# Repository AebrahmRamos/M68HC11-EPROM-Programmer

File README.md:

# M68HC11-EPROM-Programmer

## Part 1: EPROM Reader

### Overview

This project implements an EPROM reader using the M68HC11 microcontroller and a 2764 EPROM chip. The system reads the first 25 bytes of data stored in the EPROM and transmits it to a host computer via serial communication for display in both hexadecimal and ASCII formats.

### Hardware Configuration

The hardware setup maps the M68HC11 ports to the 2764 EPROM pins as follows:

- **Port B (PB0-PB7)**: Connected to EPROM address inputs A0-A7
- **Port C (PC0-PC7)**: Connected to EPROM data outputs Q0-Q7
- **Port A (PA5, PA6)**: Control signals for Chip Enable (CE) and Output Enable (OE)
- **Upper Address Lines (A8-A12)**: Grounded to restrict addressable space to the first 256 bytes

The EPROM operates with a 5V supply and has an access time of 180-250ns depending on the speed grade.

### Software Implementation

The system consists of two main components:

#### Assembly Program (programmer.asm)

The M68HC11 assembly program performs the following steps:

1. **Initialization**: Sets up the stack pointer and forces the device into single-chip mode
2. **Port Configuration**: Configures Port C as input and sets control pins to inactive (HIGH)
3. **Serial Setup**: Initializes the SCI (Serial Communication Interface) to 9600 baud
4. **Startup Delay**: Implements a `LONG_DELAY` routine to allow the bootloader time to switch baud rates
5. **Read Loop**: Iterates 25 times to:
   - Assert the address on Port B
   - Activate control signals (pull CE and OE LOW)
   - Read the data byte from Port C
   - Send the byte to the PC via `SEND_SERIAL` subroutine
   - Deactivate control signals (pull CE and OE HIGH)

#### Python Bootloader (HC11_BL-ASCII.py)

The modified bootloader script:

- Loads the assembly program into the HC11's RAM via serial at 1200 baud
- Switches the serial port to 9600 baud after successful echo-back
- Calls `read_eprom_data()` to receive and display the 25 bytes
- Displays output in hexadecimal format (8 bytes per line)
- Displays output in ASCII format (replaces non-printable characters with ".")

### Key Challenge: Baud Rate Synchronization

During initial testing, a race condition occurred where the HC11 began transmitting data before the bootloader could switch from 1200 to 9600 baud. This resulted in corrupted or "ghost" byte values.

**Solution**: Implemented the `LONG_DELAY` subroutine after baud rate configuration to waste CPU cycles, giving the bootloader sufficient time to reinitialize the serial connection at 9600 baud before the read loop begins.

### Results

The system successfully:

- Reads the first 25 bytes from the 2764 EPROM
- Transmits data error-free via serial communication
- Displays data in both hexadecimal and ASCII formats
- Handles the 0xFF value gracefully by displaying it as "." in ASCII output (since ASCII is a 7-bit standard supporting only values 0-127)

### Materials

- 1x M68HC11 Interface Board
- 1x 2764 EPROM
- 1x Breadboard
- 2x Power Supplies
- 5x 10Kohm Resistors
- 1x Oscilloscope
- 1x VOM (Voltmeter/Ohmmeter)
- 1x Computer System

### Usage

1. Assemble the assembly code into an S19 file
2. Run the bootloader script: `python HC11_BL-ASCII.py -c /dev/ttyUSB0 -i programmer.s19`
3. Press RESET on the HC11 board when prompted
4. The program will load, switch baud rates, and display the EPROM data

### Recommendations for Future Work

While the current implementation successfully resolves the baud rate race condition, it uses a fixed delay that is not deterministic. A more robust approach would implement a software handshake using interrupts, similar to TCP's three-way handshake. This would ensure 100% data synchronization without relying on timing assumptions that may fail on slower systems or under heavy CPU load.

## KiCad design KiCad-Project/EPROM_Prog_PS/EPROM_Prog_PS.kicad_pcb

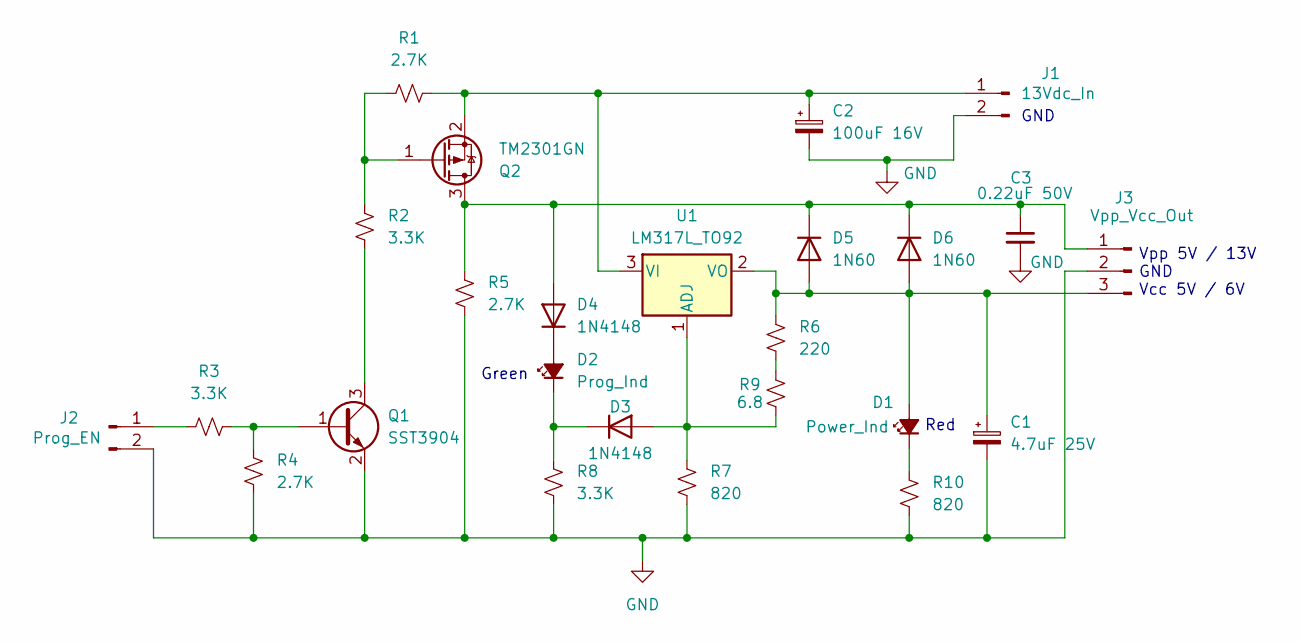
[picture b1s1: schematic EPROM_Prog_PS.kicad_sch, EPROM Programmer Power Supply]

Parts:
C1: 4.7uF 25V; CP_Radial_D5.0mm_P2.00mm
C2: 100uF 16V; CP_Radial_D6.3mm_P2.50mm
C3: 0.22uF 50V; C_Disc_D6.0mm_W4.4mm_P5.00mm
D1: Power_Ind; LED_D5.0mm
D2: Prog_Ind; LED_D5.0mm
D3, D4: 1N4148; D_DO-35_SOD27_P7.62mm_Horizontal
D5, D6: 1N60; D_DO-35_SOD27_P7.62mm_Horizontal
J1: 13Vdc_In; PinHeader_1x02_P2.54mm_Vertical
J2: Prog_EN; PinHeader_1x02_P2.54mm_Vertical
J3: Vpp_Vcc_Out; PinHeader_1x03_P2.54mm_Vertical
Q1: SST3904; SOT-23
Q2: TM2301GN; SOT-23
R1, R4, R5: 2.7K; R_Axial_DIN0207_L6.3mm_D2.5mm_P10.16mm_Horizontal
R2, R3, R8: 3.3K; R_Axial_DIN0207_L6.3mm_D2.5mm_P10.16mm_Horizontal
R6: 220; R_Axial_DIN0207_L6.3mm_D2.5mm_P10.16mm_Horizontal
R7, R10: 820; R_Axial_DIN0207_L6.3mm_D2.5mm_P10.16mm_Horizontal
R9: 6.8; R_Axial_DIN0207_L6.3mm_D2.5mm_P10.16mm_Horizontal
U1: LM317L_TO92; TO-92_Inline

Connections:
GND: C1.2, C2.2, C3.2, J1.2, J2.2, J3.2, Q1.2 (E), R4.2, R5.2, R7.2, R8.2, R10.2
unnamed: C1.1, D1.2 (A), D5.2 (A), D6.2 (A), J3.3, R6.1, U1.2 (VO)
unnamed: D1.1 (K), R10.1
unnamed: D2.2 (A), D4.1 (K)
unnamed: D2.1 (K), D3.1 (K), R8.1
unnamed: D3.2 (A), R7.1, R9.1, U1.1 (ADJ)
unnamed: C3.1, D4.2 (A), D5.1 (K), D6.1 (K), J3.1, Q2.3 (D), R5.1
unnamed: C2.1, J1.1, Q2.2 (S), R1.1, U1.3 (VI)
unnamed: J2.1, R3.1
unnamed: Q1.1 (B), R3.2, R4.1
unnamed: Q1.3 (C), R2.2
unnamed: Q2.1 (G), R1.2, R2.1
unnamed: R6.2, R9.2

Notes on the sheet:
Green
Vpp 5V / 13V GND Vcc 5V / 6V
GND
Red

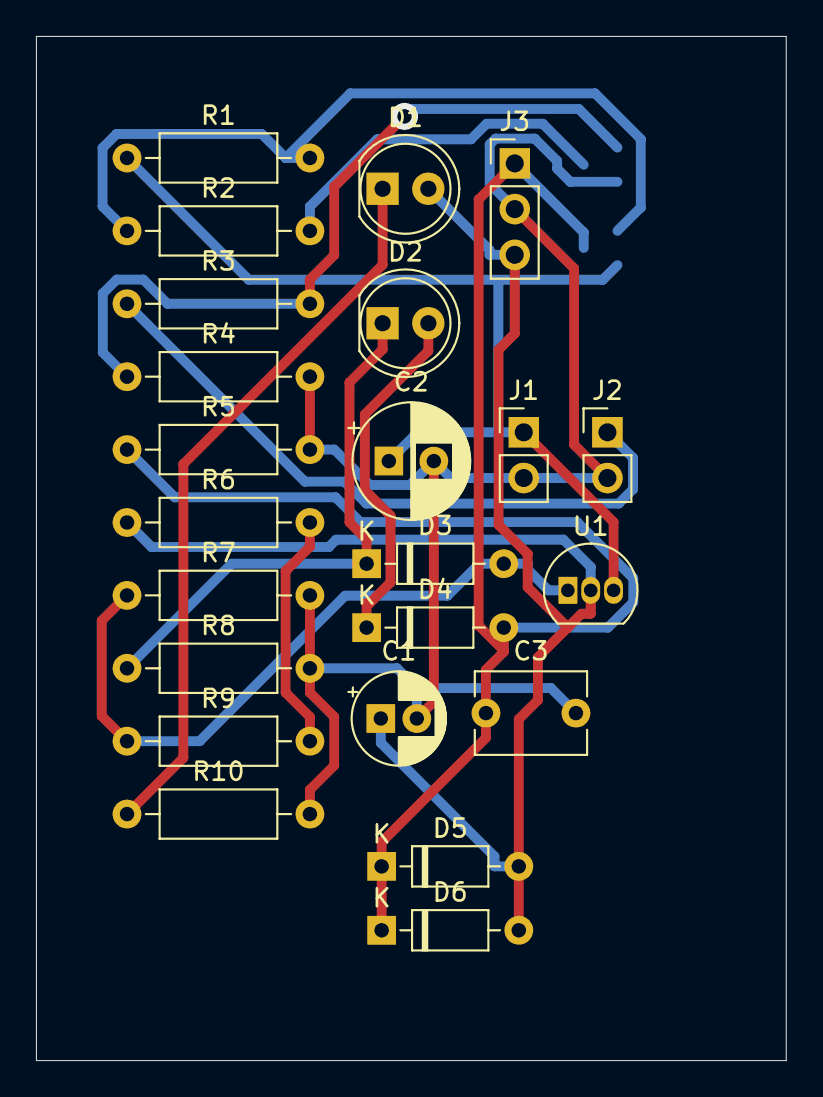
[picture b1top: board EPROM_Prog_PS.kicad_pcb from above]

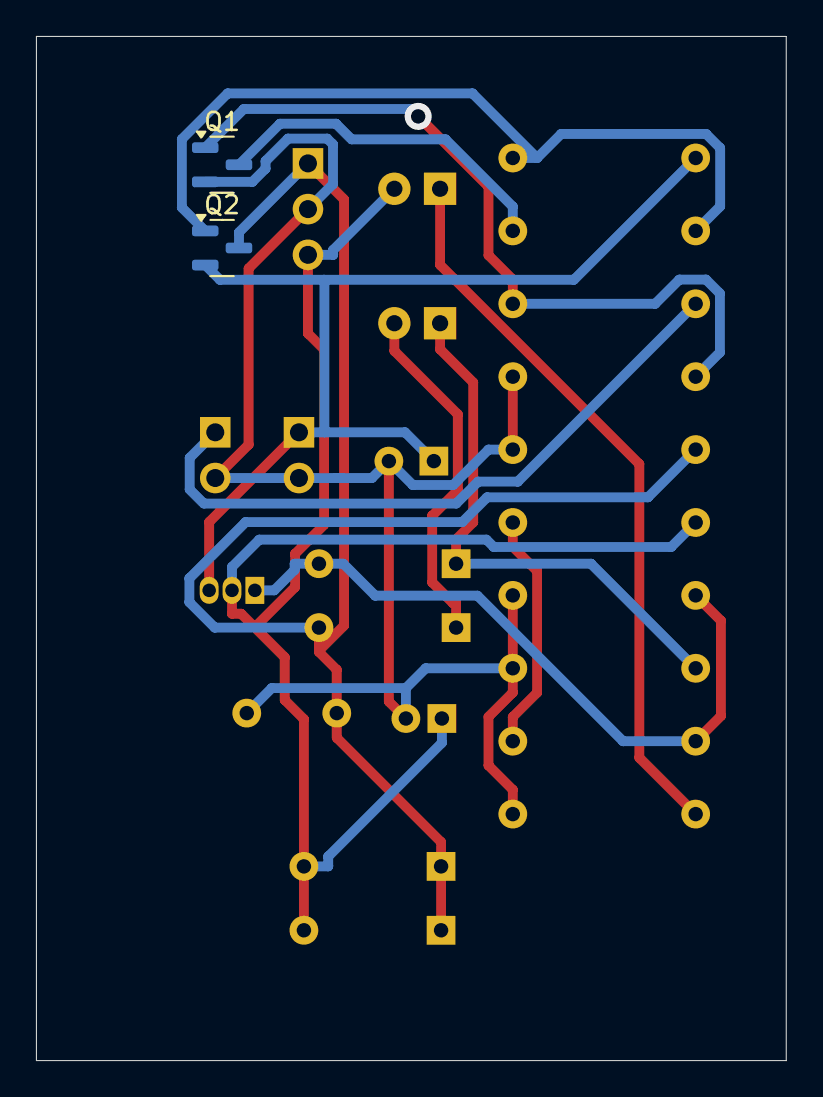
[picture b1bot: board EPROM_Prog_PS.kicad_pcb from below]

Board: 2 copper layers, 41.7 x 56.9 mm, 25 parts (2 on the bottom side), 13 nets.

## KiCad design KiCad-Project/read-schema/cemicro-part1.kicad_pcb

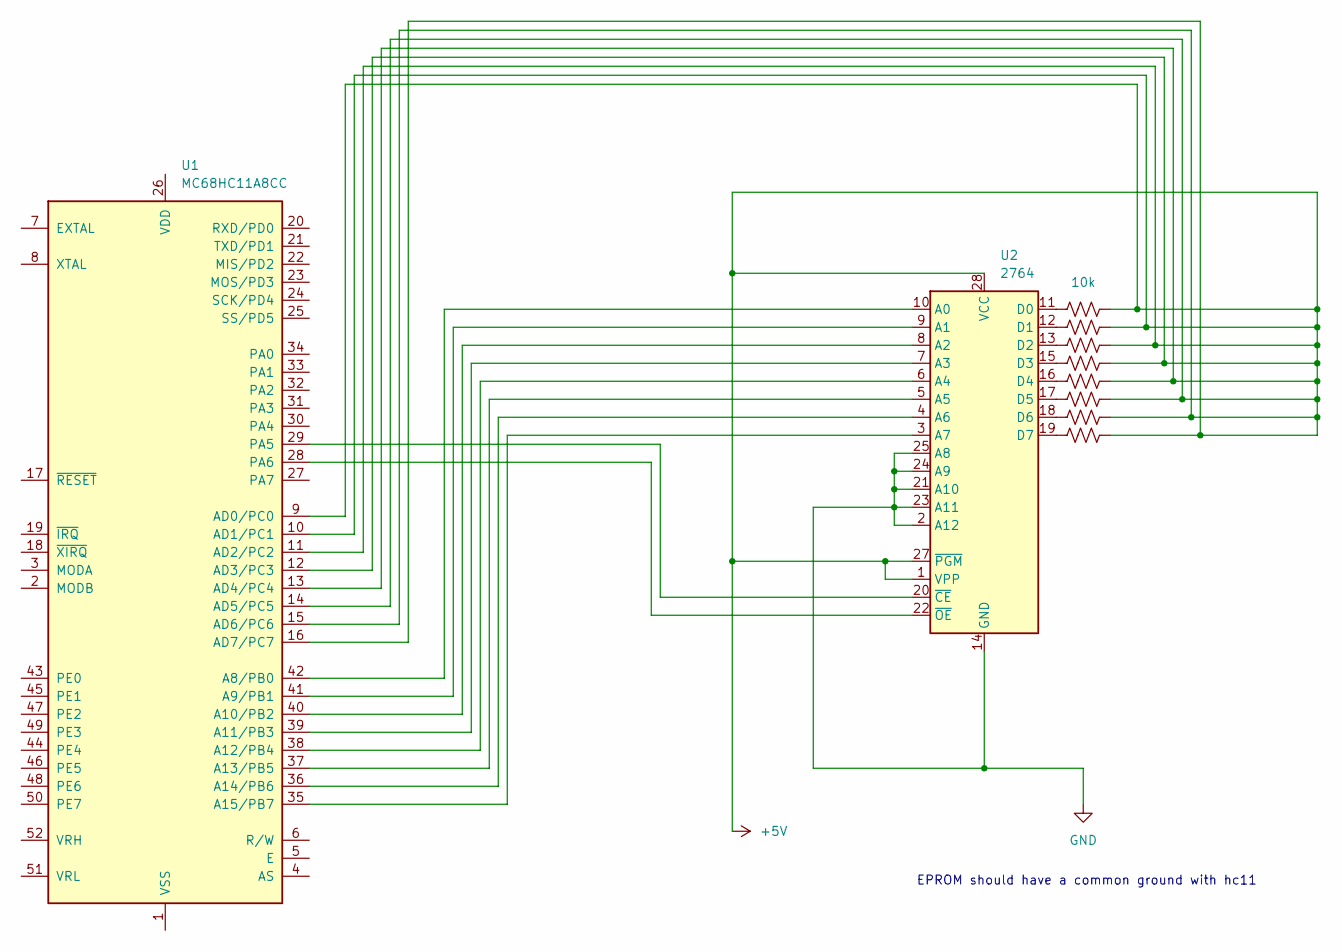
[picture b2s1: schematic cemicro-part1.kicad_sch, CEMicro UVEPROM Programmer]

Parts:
R1: 10k; R_LDR_4.9x4.2mm_P2.54mm_Vertical
R2, R3, R4, R5, R6, R7, R8: 1k; R_LDR_4.9x4.2mm_P2.54mm_Vertical
U1: MC68HC11A8CC
U2: 2764; DIP-28_W15.24mm

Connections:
+5V: R1.2, R2.2, R3.2, R4.2, R5.2, R6.2, R7.2, R8.2, U1.9 (AD0/PC0), U1.10 (AD1/PC1), U1.11 (AD2/PC2), U1.12 (AD3/PC3), U1.13 (AD4/PC4), U1.14 (AD5/PC5), U1.15 (AD6/PC6), U1.16 (AD7/PC7), U2.1 (VPP), U2.27 (~PGM), U2.28 (VCC)
GND: U2.2 (A12), U2.14 (GND), U2.21 (A10), U2.23 (A11), U2.24 (A9), U2.25 (A8)
unnamed: U1.42 (A8/PB0), U2.10 (A0)
unnamed: U1.41 (A9/PB1), U2.9 (A1)
unnamed: U1.40 (A10/PB2), U2.8 (A2)
unnamed: U1.39 (A11/PB3), U2.7 (A3)
unnamed: U1.38 (A12/PB4), U2.6 (A4)
unnamed: U1.37 (A13/PB5), U2.5 (A5)
unnamed: U1.36 (A14/PB6), U2.4 (A6)
unnamed: U1.35 (A15/PB7), U2.3 (A7)
unnamed: U1.29 (PA5), U2.20 (~CE)
unnamed: U1.28 (PA6), U2.22 (~OE)
unnamed: R1.1, U2.11 (D0)
unnamed: R2.1, U2.12 (D1)
unnamed: R3.1, U2.13 (D2)
unnamed: R4.1, U2.15 (D3)
unnamed: R5.1, U2.16 (D4)
unnamed: R6.1, U2.17 (D5)
unnamed: R7.1, U2.18 (D6)
unnamed: R8.1, U2.19 (D7)

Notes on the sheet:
EPROM should have a common ground with hc11

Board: 2 copper layers, 9 parts (0 on the bottom side), 10 nets, no tracks yet.

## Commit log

2025-12-01 feat(): implements eprom reader and schema
2025-12-01 feat(programmer.asm): add M27C64A programming routine (1ms pulse, verify, retry, 3ms over-program)
    - added 2764A datasheet
    - added M68HC11 datasheet
    - wrote a programmers notebook to be cache my thought process
2025-12-01 feat: add PCB routes based from schematic
2025-12-02 fix: pcb DRC errors
2025-12-02 feat: finalize pcb for printing
2025-12-03 feat: include asm11_win32.exe
2025-12-03 feat: include read-only asm file
2025-12-05 feat(programmer.asm): update programming constants and enhance pulse logic for EPROM programming
2025-12-05 drafts
2025-12-06 update code and kicad: add bit 3 for program control
